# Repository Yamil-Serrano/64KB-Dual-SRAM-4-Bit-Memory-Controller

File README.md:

# 64KB Dual-SRAM 4-Bit Memory Controller

A memory controller module that interfaces a 4-bit CPU with standard 8-bit SRAM chips, enabling individual nibble read and write operations without wasting the unused half of each memory byte. The design implements a transparent read-modify-write cycle within a single clock period using discrete 74HC-series logic, making it suitable for breadboard prototyping and custom PCB integration.

## Overview

This RAM module bridges the gap between 4-bit data paths and 8-bit memory organization. While the SRAM stores 8-bit bytes, the CPU operates on 4-bit nibbles. This controller allows the CPU to access either the upper or lower nibble of any byte independently, treating the memory space as individually addressable nibble locations when combined with the appropriate control signals.

The core challenge addressed by this design is the inability of standard SRAM to perform partial-byte writes. A 4-bit CPU attempting to modify only four bits of an eight-bit memory location would normally corrupt the adjacent nibble. This module solves this problem by performing an automatic read-modify-write operation entirely within a single clock cycle, completely transparent to the programmer.

To achieve the full 64 KB address space, the design uses **two 32K x 8 SRAM chips** connected in parallel. The MSB of the address bus (`ADDR[15]`) acts as a bank selector, using the `~CE` (Chip Enable) pins to ensure that only one SRAM drives the data bus at any given time.

## Architecture

The memory module consists of two primary data paths: a read path that delivers the selected nibble to the CPU, and a write path that reconstructs a complete byte from the old byte and the new nibble before writing it back to SRAM.

### Read Path

During read operations, the active SRAM outputs a full byte through the 74HC245 bidirectional transceiver. That byte is then fed into a 74HC157 2:1 multiplexer, which selects either the upper or lower nibble based on the SEL signal and presents the chosen nibble to the CPU's 4-bit data bus.

### Write Path

Write operations reconstruct a full byte before it ever reaches the SRAM. First, the existing byte is read out of SRAM through the 74HC245 and captured by a 74HC573 transparent latch. That latched byte is then combined with the new nibble coming from the CPU through two 74HC257 multiplexers, which merge the old byte and the new nibble into a complete byte. Finally, that reconstructed byte is driven back through the 74HC245, now switched to the opposite direction, and written into SRAM. The whole sequence is coordinated by the clock signal, which splits the operation into a rising-edge phase for reading the old byte and a falling-edge phase for writing the modified byte back.

### Memory Expansion (64 KB)

The base design uses a single 32 KB SRAM. To expand to 64 KB, a second SRAM is added in parallel, sharing the address bus, data bus, `~WE`, and `~OE` signals.

- **SRAM1 (Lower 32 KB):** `~CE` is connected directly to `ADDR[15]`. Selected when `ADDR[15] = 0`.
- **SRAM2 (Upper 32 KB):** `~CE` is connected to the output of a NAND gate used as an inverter, driven by `ADDR[15]`. Selected when `ADDR[15] = 1`.

The `~OE` pins of both SRAMs are tied to GND. The chip select logic guarantees that only one SRAM drives the data bus at a time, making the expansion completely plug-and-play with no changes to the control logic or CPU firmware.

## Schematic

### PCB Design in Kicad

## Components Used

| IC | Function | Quantity | Purpose |
|---|---|---|---|
| CY62256LL-70 | SRAM (32K x 8) | 2 | 64 KB total memory storage |
| 74HC245 | Octal Bus Transceiver | 1 | Bidirectional data bus control |
| 74HC573 | Octal Transparent Latch | 1 | Captures and holds old byte during write operations |
| 74HC257 | Quad 2:1 Multiplexer | 2 | Byte reconstruction from old byte and new nibble |
| 74HC157 | Quad 2:1 Multiplexer | 1 | Nibble selection during read operations |
| 74HC00 | Quad NAND Gate | 1 | Control signal generation and bank selection |

## Specifications

### Memory Characteristics

- **Memory Devices:** 2x CY62256LL-70 (32K x 8 SRAM)
- **Total Capacity:** 64 KB (65,536 bytes)
- **Address Lines:** 16 lines (A0-A15). A0-A14 are shared between both SRAMs, while A15 acts as the bank selector.
- **Organization:** 8-bit bytes, each containing two 4-bit nibbles.

### Interface Signals

| Signal | Direction | Description |
|---|---|---|
| SW | Input | Write enable (1 = write, 0 = read) |
| CLK | Input | System clock, controls phase timing |
| SEL | Input | Nibble select (0 = low nibble, 1 = high nibble) |
| ADDR | Input | Memory address (16 lines, A0-A15) |

## Control Logic

The 74HC00 generates all required control signals from the SW and CLK inputs. The core logic equations are:

```
NAND1 = NOT(CLK)
NAND2 = NOT(SW AND NAND1)
CTRL = NAND2
DIR = NOT(CTRL)
```

The CTRL signal controls SRAM write enable, latch enable, and multiplexer output enable. The DIR signal controls the direction of the bidirectional transceiver. On the clock's rising edge, CTRL is high and DIR is low: the SRAM stays in read mode, the 74HC245 points from SRAM to the circuit, and the 74HC573 latch is transparent, capturing the old byte. On the falling edge, CTRL goes low and DIR goes high: the SRAM switches to write mode, the 74HC245 reverses direction toward the SRAM, the latch holds the captured byte, and the 74HC257 multiplexers become active to merge in the new nibble.

## Operation Details

### Write Operation (SW = 1)

When the CPU initiates a write operation, the module executes the following sequence within a single clock cycle:

**Phase 1: Rising Edge - Read Old Byte**
- Active SRAM remains in read mode (WE = 1)
- 74HC245 configured for SRAM -> Circuit direction
- 74HC573 latch is transparent and captures the full byte from SRAM

**Phase 2: Falling Edge - Write Modified Byte**
- Active SRAM transitions to write mode (WE = 0)
- 74HC245 configured for Circuit -> SRAM direction
- 74HC573 holds the old byte value
- 74HC257 multiplexers reconstruct the new byte

### Read Operation (SW = 0)

Read operations are straightforward and do not require the read-modify-write process:

1. Active SRAM outputs the full byte to the 74HC245
2. 74HC245 passes the byte to the 74HC157 multiplexer
3. The multiplexer selects either the high or low nibble based on SEL
4. The selected nibble appears on the CPU data bus

## Timing Analysis and Maximum Frequency

Although the module is designed for robust operation in a modular breadboard/PCB environment, the theoretical maximum operating frequency is bounded by the critical path of the Read-Modify-Write (RMW) cycle. Since the clock has a 50% duty cycle, the total period (T_CLK) is limited by the slowest of the two phases multiplied by two.

### 1. Control Logic Delay (Common to both phases)
The CLK signal propagates through three cascaded NAND gates inside the 74HC00 to generate the CTRL and DIR signals.
*   Control time = 3 * 10ns = 30ns (Worst-case typical at 5V)

### 2. Phase 1: Read Old Byte (Rising Edge)
Data flows from the SRAM -> 74HC245 -> 74HC573. The SRAM must output valid data, it must pass through the transceiver, and the latch must capture it before the clock falls.
*   Control time: 30ns
*   SRAM access time (CY62256LL-70): 70ns
*   74HC245 propagation delay: 12ns
*   74HC573 setup time: 20ns
*   **Total Phase 1:** 30 + 70 + 12 + 20 = **132ns**

### 3. Phase 2: Write Reconstructed Byte (Falling Edge)
Data flows from the 74HC573 -> 74HC257 -> 74HC245 -> SRAM. The latch must output the data, the multiplexers must merge it, the transceiver must drive it, and the SRAM must capture it before ~WE goes high.
*   Control time: 30ns
*   74HC573 propagation delay: 15ns
*   74HC257 propagation delay: 12ns
*   74HC245 propagation delay: 12ns
*   SRAM setup time (Data valid before ~WE rises): 20ns
*   **Total Phase 2:** 30 + 15 + 12 + 12 + 20 = **89ns**

### 4. Theoretical Maximum Frequency
The critical path is Phase 1 (132ns). Therefore, the minimum clock period is:
Minimum Period (T_min) = 2 * 132ns = **264ns**

Maximum Frequency (F_max) = 1 / 264ns = 0.003787 GHz = **3.787 MHz**

> **Note:** Adding ~10-20ns for PCB parasitics and clock skew across modular jumpers brings the practical, stable maximum frequency to approximately **3.0 - 3.5 MHz**.**

## Educational Value

This project demonstrates several important concepts in digital design:

- **Memory Interfacing:** Connecting a CPU to memory with different data widths
- **Read-Modify-Write:** Performing atomic operations on memory
- **Transparent Hardware:** Implementing complex operations inside a single clock cycle
- **Bidirectional Data Buses:** Managing data flow direction on shared buses
- **Bank Switching:** Expanding memory using chip select signals
- **Timing Analysis:** Understanding propagation delays and critical paths
- **Signal Generation:** Deriving multiple control signals from basic logic gates

## Known Limitations

- **Maximum Frequency:** Ripple-through propagation limits top speed to approximately 3.78 MHz
- **No Wait States:** The module assumes the CPU can complete the operation in one cycle

## License

Licensed under the Solderpad Hardware License v2.1.
See the LICENSE file for full terms.

## Contact

If you have any questions or suggestions, feel free to reach out:

- GitHub: [Neowizen](https://github.com/Neowizen)

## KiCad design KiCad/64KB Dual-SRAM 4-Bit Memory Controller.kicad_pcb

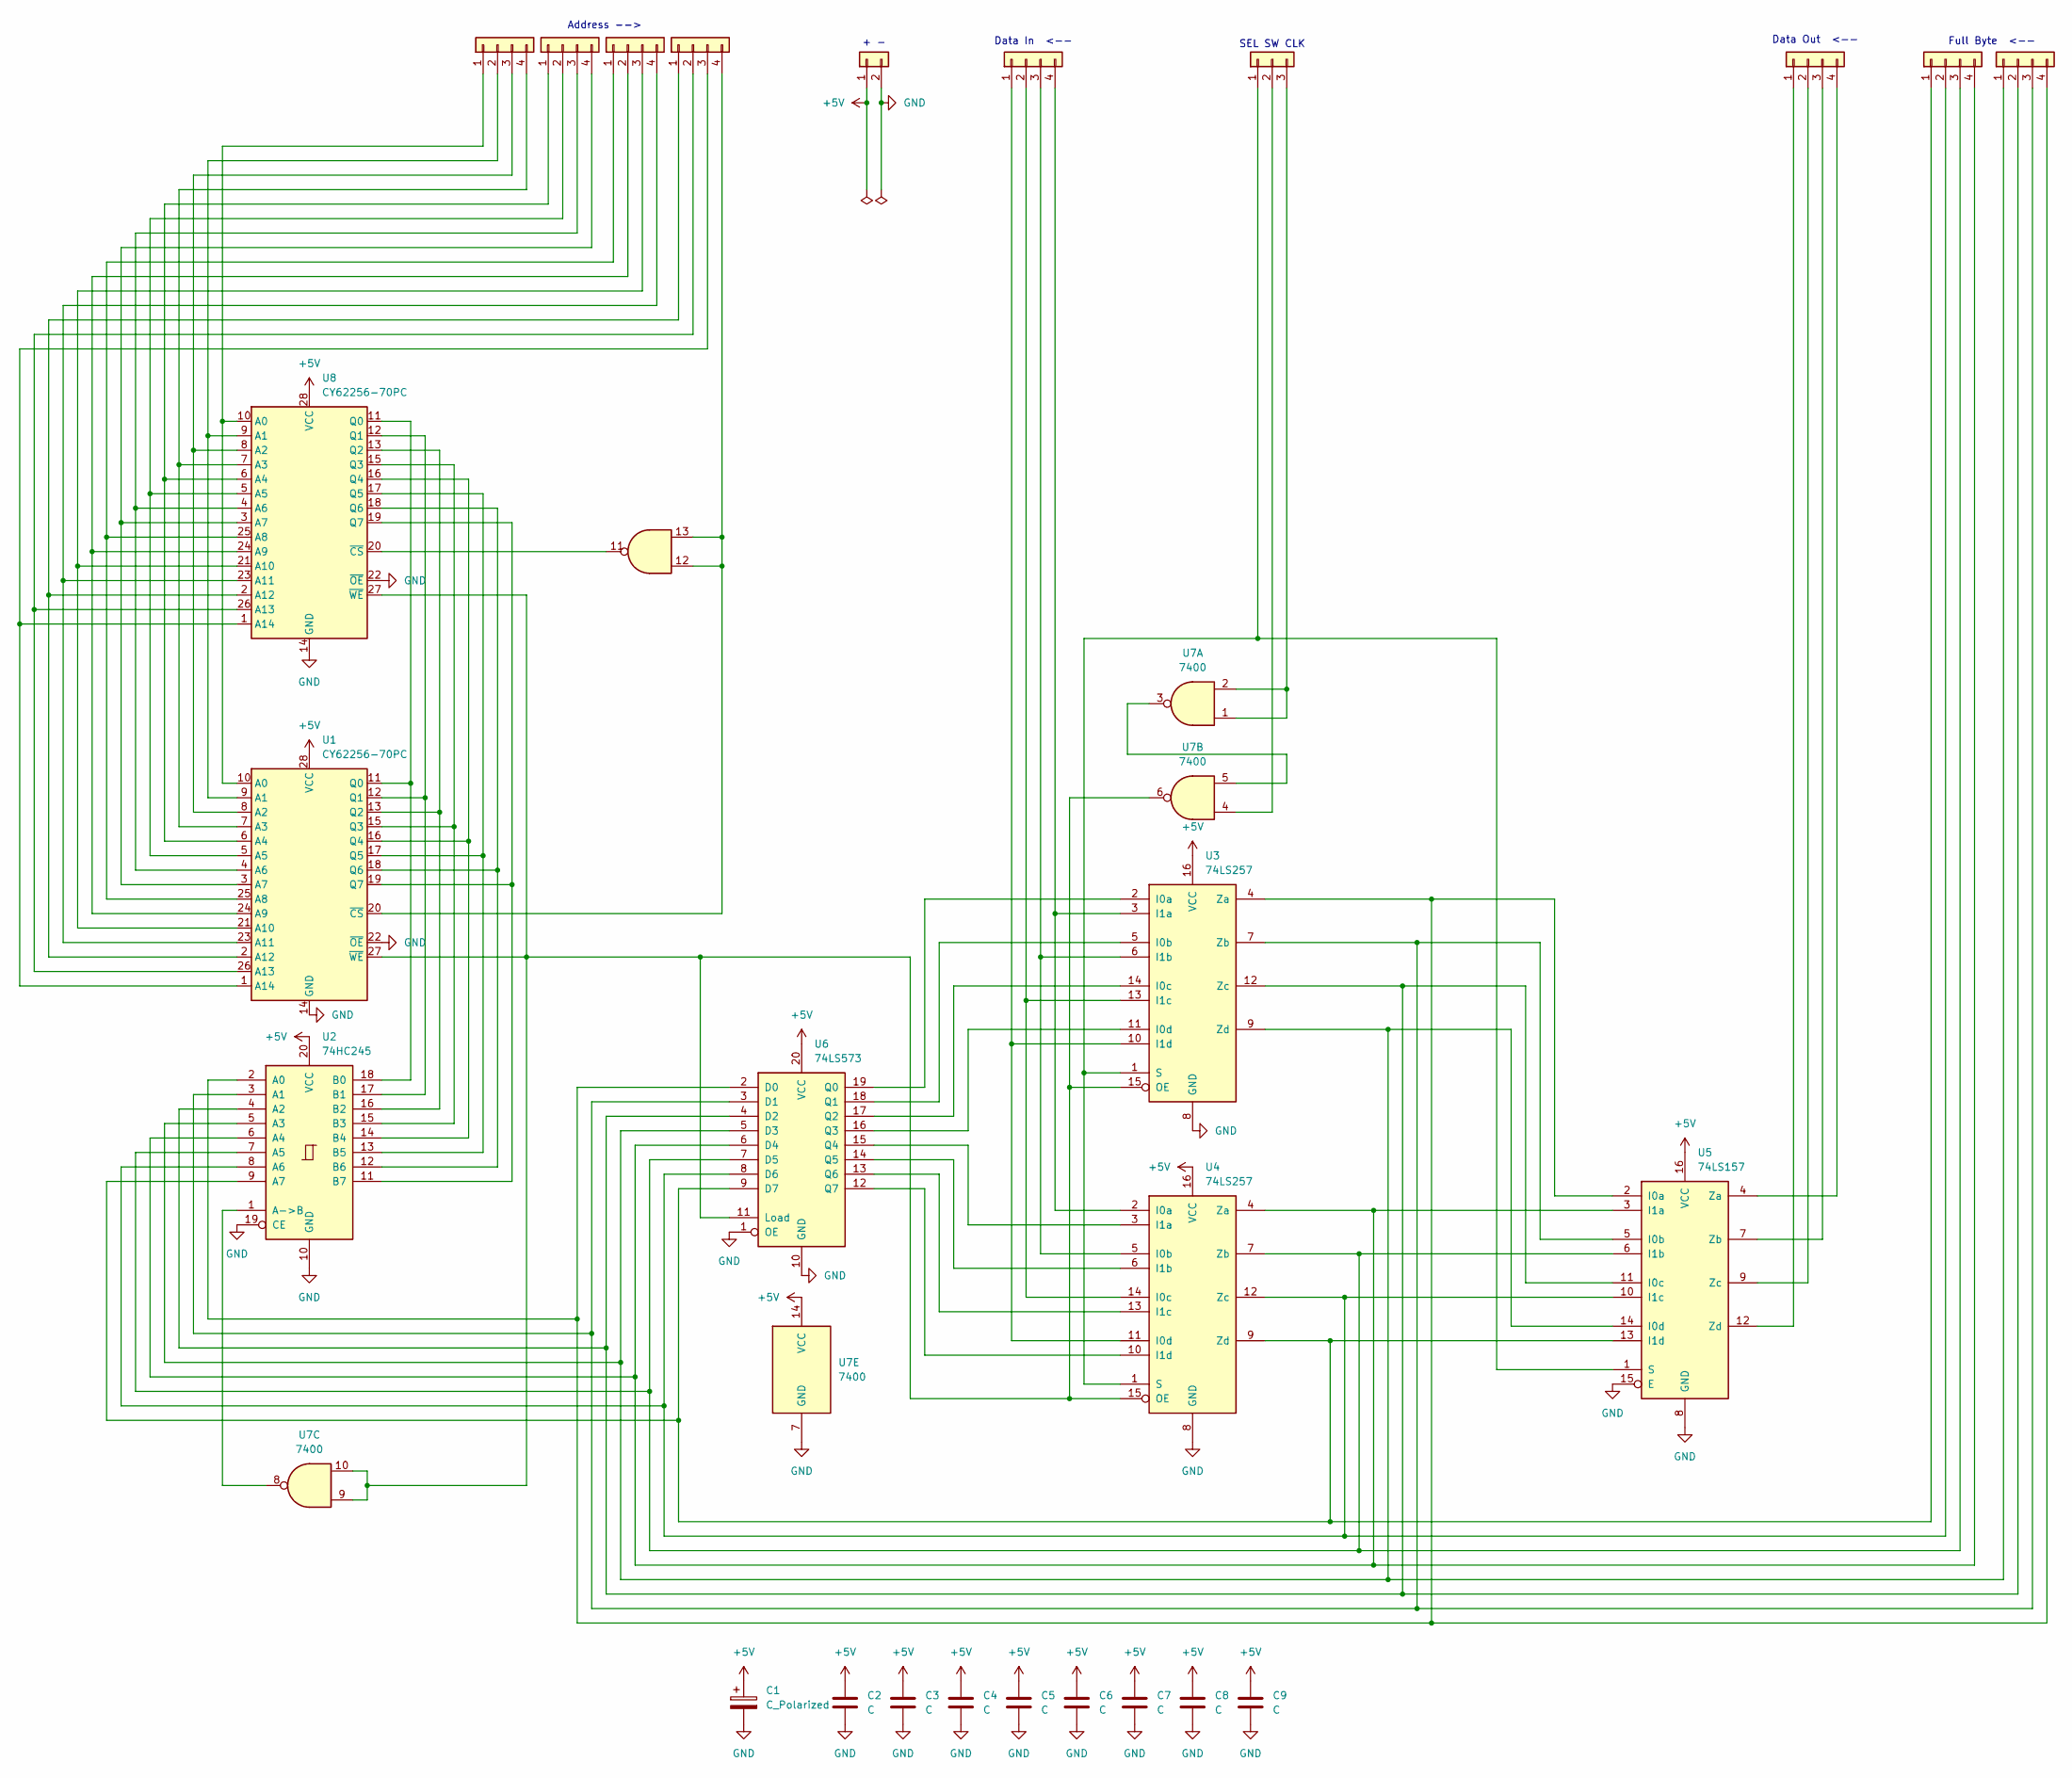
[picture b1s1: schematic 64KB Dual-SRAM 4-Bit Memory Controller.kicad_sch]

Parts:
C1: C_Polarized; CP_Radial_D4.0mm_P1.50mm
C2, C3, C4, C5, C6, C7, C8, C9: C; C_Disc_D3.0mm_W1.6mm_P2.50mm
J1, J4, J5, J6, J7, J8, J9, J10: Conn_01x04; PinHeader_1x04_P2.54mm_Vertical
J2: Conn_01x02; PinHeader_1x02_P2.54mm_Vertical
J3: Conn_01x03; PinHeader_1x03_P2.54mm_Vertical
U1, U8: CY62256-70PC; DIP-28_W15.24mm_Socket
U2: 74HC245; DIP-20_W7.62mm_Socket
U3, U4: 74LS257; DIP-16_W7.62mm_Socket
U5: 74LS157; DIP-16_W7.62mm_Socket
U6: 74LS573; DIP-20_W7.62mm_Socket
U7: 7400; DIP-14_W7.62mm_Socket

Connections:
+5V: C1.1, C2.1, C3.1, C4.1, C5.1, C6.1, C7.1, C8.1, C9.1, J2.1, U1.28 (VCC), U2.20 (VCC), U3.16 (VCC), U4.16 (VCC), U5.16 (VCC), U6.20 (VCC), U7.14 (VCC), U8.28 (VCC)
GND: C1.2, C2.2, C3.2, C4.2, C5.2, C6.2, C7.2, C8.2, C9.2, J2.2, U1.14 (GND), U1.22 (~OE), U2.10 (GND), U2.19 (CE), U3.8 (GND), U4.8 (GND), U5.8 (GND), U5.15 (E), U6.1 (OE), U6.10 (GND), U7.7 (GND), U8.14 (GND), U8.22 (~OE)
unnamed: J1.1, U3.10 (I1d), U4.11 (I0d)
unnamed: J1.2, U3.13 (I1c), U4.14 (I0c)
unnamed: J1.3, U3.6 (I1b), U4.5 (I0b)
unnamed: J1.4, U3.3 (I1a), U4.2 (I0a)
unnamed: J3.1, U3.1 (S), U4.1 (S), U5.1 (S)
unnamed: J3.2, U7.4
unnamed: J3.3, U7.1, U7.2
unnamed: J4.1, U1.2 (A12), U8.2 (A12)
unnamed: J4.2, U1.26 (A13), U8.26 (A13)
unnamed: J4.3, U1.1 (A14), U8.1 (A14)
unnamed: J4.4, U1.20 (~CS), U7.12, U7.13
unnamed: J5.1, U1.25 (A8), U8.25 (A8)
unnamed: J5.2, U1.24 (A9), U8.24 (A9)
unnamed: J5.3, U1.21 (A10), U8.21 (A10)
unnamed: J5.4, U1.23 (A11), U8.23 (A11)
unnamed: J6.1, U1.6 (A4), U8.6 (A4)
unnamed: J6.2, U1.5 (A5), U8.5 (A5)
unnamed: J6.3, U1.4 (A6), U8.4 (A6)
unnamed: J6.4, U1.3 (A7), U8.3 (A7)
unnamed: J7.1, U1.10 (A0), U8.10 (A0)
unnamed: J7.2, U1.9 (A1), U8.9 (A1)
unnamed: J7.3, U1.8 (A2), U8.8 (A2)
unnamed: J7.4, U1.7 (A3), U8.7 (A3)
unnamed: J8.1, U5.12 (Zd)
unnamed: J8.2, U5.9 (Zc)
unnamed: J8.3, U5.7 (Zb)
unnamed: J8.4, U5.4 (Za)
unnamed: J9.1, U2.9 (A7), U4.9 (Zd), U5.13 (I1d), U6.9 (D7)
unnamed: J9.2, U2.8 (A6), U4.12 (Zc), U5.10 (I1c), U6.8 (D6)
unnamed: J9.3, U2.7 (A5), U4.7 (Zb), U5.6 (I1b), U6.7 (D5)
unnamed: J9.4, U2.6 (A4), U4.4 (Za), U5.3 (I1a), U6.6 (D4)
unnamed: J10.1, U2.5 (A3), U3.9 (Zd), U5.14 (I0d), U6.5 (D3)
unnamed: J10.2, U2.4 (A2), U3.12 (Zc), U5.11 (I0c), U6.4 (D2)
unnamed: J10.3, U2.3 (A1), U3.7 (Zb), U5.5 (I0b), U6.3 (D1)
unnamed: J10.4, U2.2 (A0), U3.4 (Za), U5.2 (I0a), U6.2 (D0)
unnamed: U1.11 (Q0), U2.18 (B0), U8.11 (Q0)
unnamed: U1.12 (Q1), U2.17 (B1), U8.12 (Q1)
unnamed: U1.13 (Q2), U2.16 (B2), U8.13 (Q2)
unnamed: U1.15 (Q3), U2.15 (B3), U8.15 (Q3)
unnamed: U1.16 (Q4), U2.14 (B4), U8.16 (Q4)
unnamed: U1.17 (Q5), U2.13 (B5), U8.17 (Q5)
unnamed: U1.18 (Q6), U2.12 (B6), U8.18 (Q6)
unnamed: U1.19 (Q7), U2.11 (B7), U8.19 (Q7)
unnamed: U1.27 (~WE), U3.15 (OE), U4.15 (OE), U6.11 (Load), U7.6, U7.9, U7.10, U8.27 (~WE)
unnamed: U2.1 (A->B), U7.8
unnamed: U3.2 (I0a), U6.19 (Q0)
unnamed: U3.5 (I0b), U6.18 (Q1)
unnamed: U3.14 (I0c), U6.17 (Q2)
unnamed: U3.11 (I0d), U6.16 (Q3)
unnamed: U4.3 (I1a), U6.15 (Q4)
unnamed: U4.6 (I1b), U6.14 (Q5)
unnamed: U4.13 (I1c), U6.13 (Q6)
unnamed: U4.10 (I1d), U6.12 (Q7)
unnamed: U7.3, U7.5
unnamed: U7.11, U8.20 (~CS)

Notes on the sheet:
Address -->
SEL SW CLK
Data In <--
Data Out <--
Full Byte <--
+ -

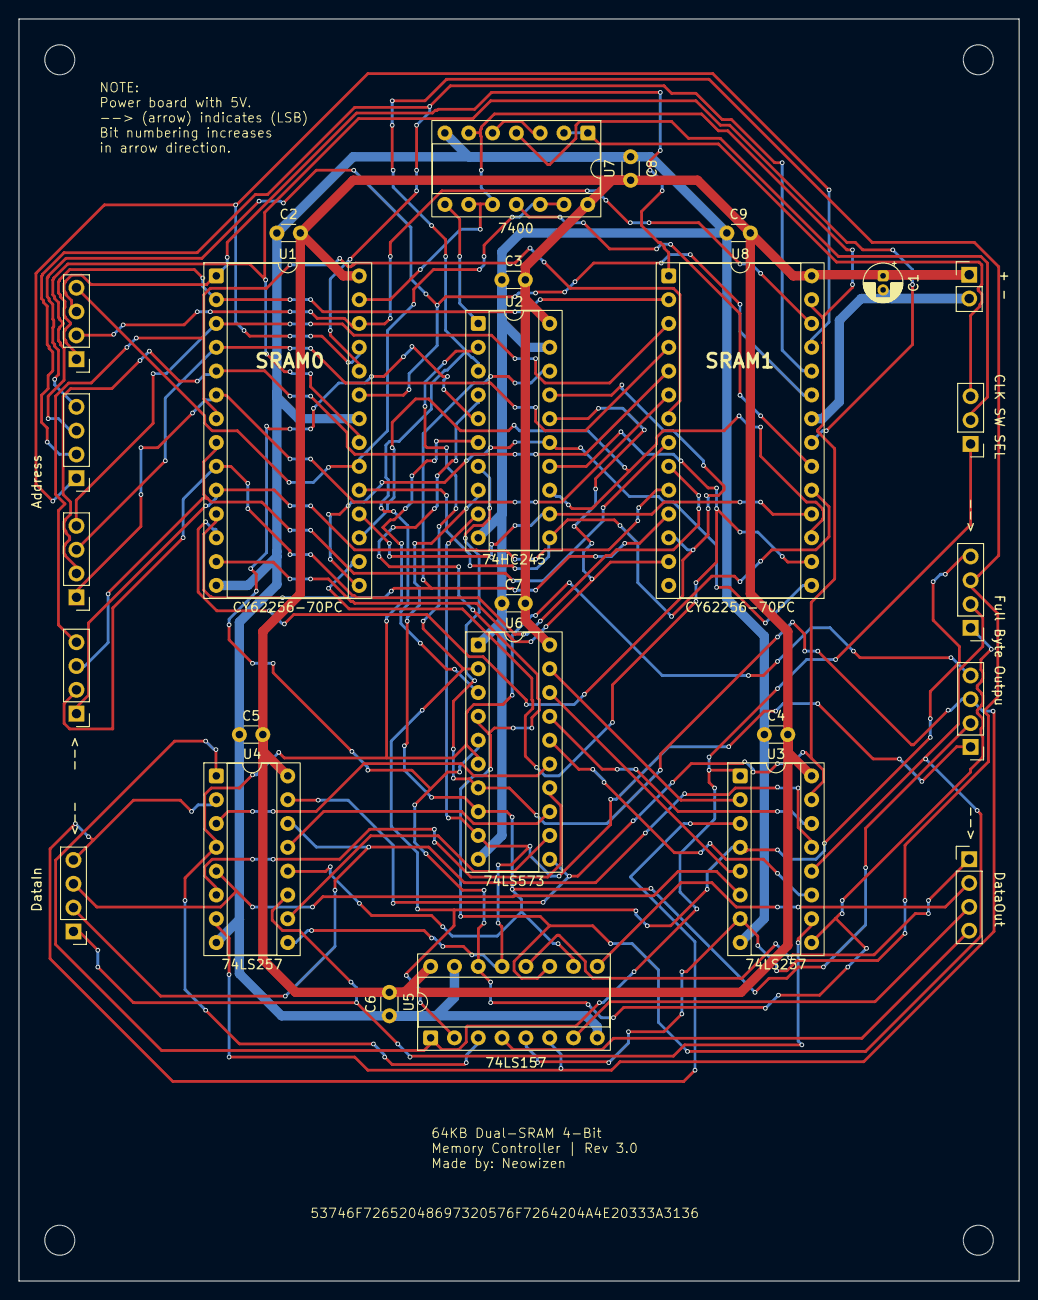
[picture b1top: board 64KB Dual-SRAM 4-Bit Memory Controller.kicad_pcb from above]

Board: 2 copper layers, 106.7 x 134.6 mm, 27 parts (0 on the bottom side), 57 nets.
